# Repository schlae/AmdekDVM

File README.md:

# Amdek DVM Clone

The Amdek DVM allowed RGB digital monitors to be connected to Apple II
computers (which normally output composite video).

This project is a reverse-engineered version of this card.

It uses readily-available TTL logic chips, with no programmable devices at
all.

*Note: The photo shows an original DVM card since I have not fabricated my design*

[Schematic](AmdekDVM.pdf)

[Bill of Materials](AmdekDVM.csv)

[Fab files](fab/AmdekDVM-Rev1.zip)

[Fab files for daughterboard](AmdekDaughterBoard/fab/AmdekDaughterBoard-Rev1.zip)

## Fabrication Notes

The main board is 280mm x 76mm (11" x 3"). It is a simple 2-layer board. It
has an edge connector on the bottom, and you may want to have it gold plated,
but this isn't strictly necessary. No edge bevel is required but it may make
it easier to insert into the connectors on the Apple II (or you could add
one with a file).

The daughterboard is 38mm x 87mm (1.5" x 3.435"). It is a simple 2-layer board
and could even be reduced down to a 1-layer design if you have access to such
a fab process.

## Assembly Notes

RV2 is actually a fixed resistor, 2K. Solder it from pin 1 to pin 3.

C3-C13 are just bypass capacitors and could easily be subbed out with 0.1uF.

C14-C23 are not stuffed on the original board, but it would be harmless
to place 0.1uF capacitors here.

The daughterboard (actually two separate boards, see the photos below) should
have machine-pin sockets installed. To allow them to be plugged into the Apple
II motherboard, solder additional socket pins (harvested from spare sockets)
to the ends of the pins protruding from the other side of the board. Alignment
is critical so that the pins will plug into the sockets on the Apple II.

The daughterboard can be assembled with regular 0.1" headers and 8-pin IDC
plugs, or you can use a combined part like the CA2308PA10Z. The cable is
split exactly in half, with the first 8 pins going to the 4-chip daughterboard
and the second 8 pins going to the 2-chip daughterboard (with wire 9 tied
to pin 1 of this daughterboard).

## Cables

To build this card, you will need a video output cable wired as follows. Plug
it into J2 (nearest the edge connector).

| Pin | Description |
|-----|-------------|
| 1   | Red output |
| 2   | Green output |
| 3   | Blue output |
| 4   | Horizontal sync (positive) |
| 5   | Horizontal sync (negative) |
| 6   | Vertical sync (positive) |
| 7   | Vertical sync (negative) |
| 8   | No connect |
| 9   | Ground |
| 10  | No connect |
| 11  | Apple II text - connect to Apple II header K14 pin 2 |
| 12  | Horizontal sync from 80-column card |
| 13  | Video signal from 80-column card |
| 14  | Vertical sync from 80-column card |

Pin 11 of this cable should be wired to the Apple II video header. On my
Apple II+, it looks like this.

If you want to connect the DVM to a CGA-compatible monitor, wire it up as
follows:

| Amdek Pin | CGA Pin | Description |
|-----------|---------|-------------|
| 1         |  3      | Red output  |
| 2         |  4      | Green output |
| 3         |  5      | Blue output |
| 4         |  8      | Horizontal sync (positive) |
| 6         |  9      | Vertical sync (positive) |
| 9         |  1      | Ground |

If you have an 80-column card, you can wire pins 12-14 to that card as
appropriate.

You will also need a cable connected to J1 (furthest from the edge connector)
wired to two daughterboards. The daughterboards act as interposers, tapping
various signals on the Apple II motherboard.

* One daughterboard sits on motherboard positions D11, D12, D13, and D14,
hosting the four 74LS161 chips that the Apple II uses to generate the video
timing signals. It intercepts three horizontal counter bits and five vertical
counter bits.

* The other daughterboard sits on motherboard positions B6 and B7, hosting
two 74LS257 chips. This intercepts the eight digital video bits before
they go through encoding to composite video.

## Adjustments

When you install the card, ensure you get video out of your Apple II, then
adjust RV1 until you get stable pixels.

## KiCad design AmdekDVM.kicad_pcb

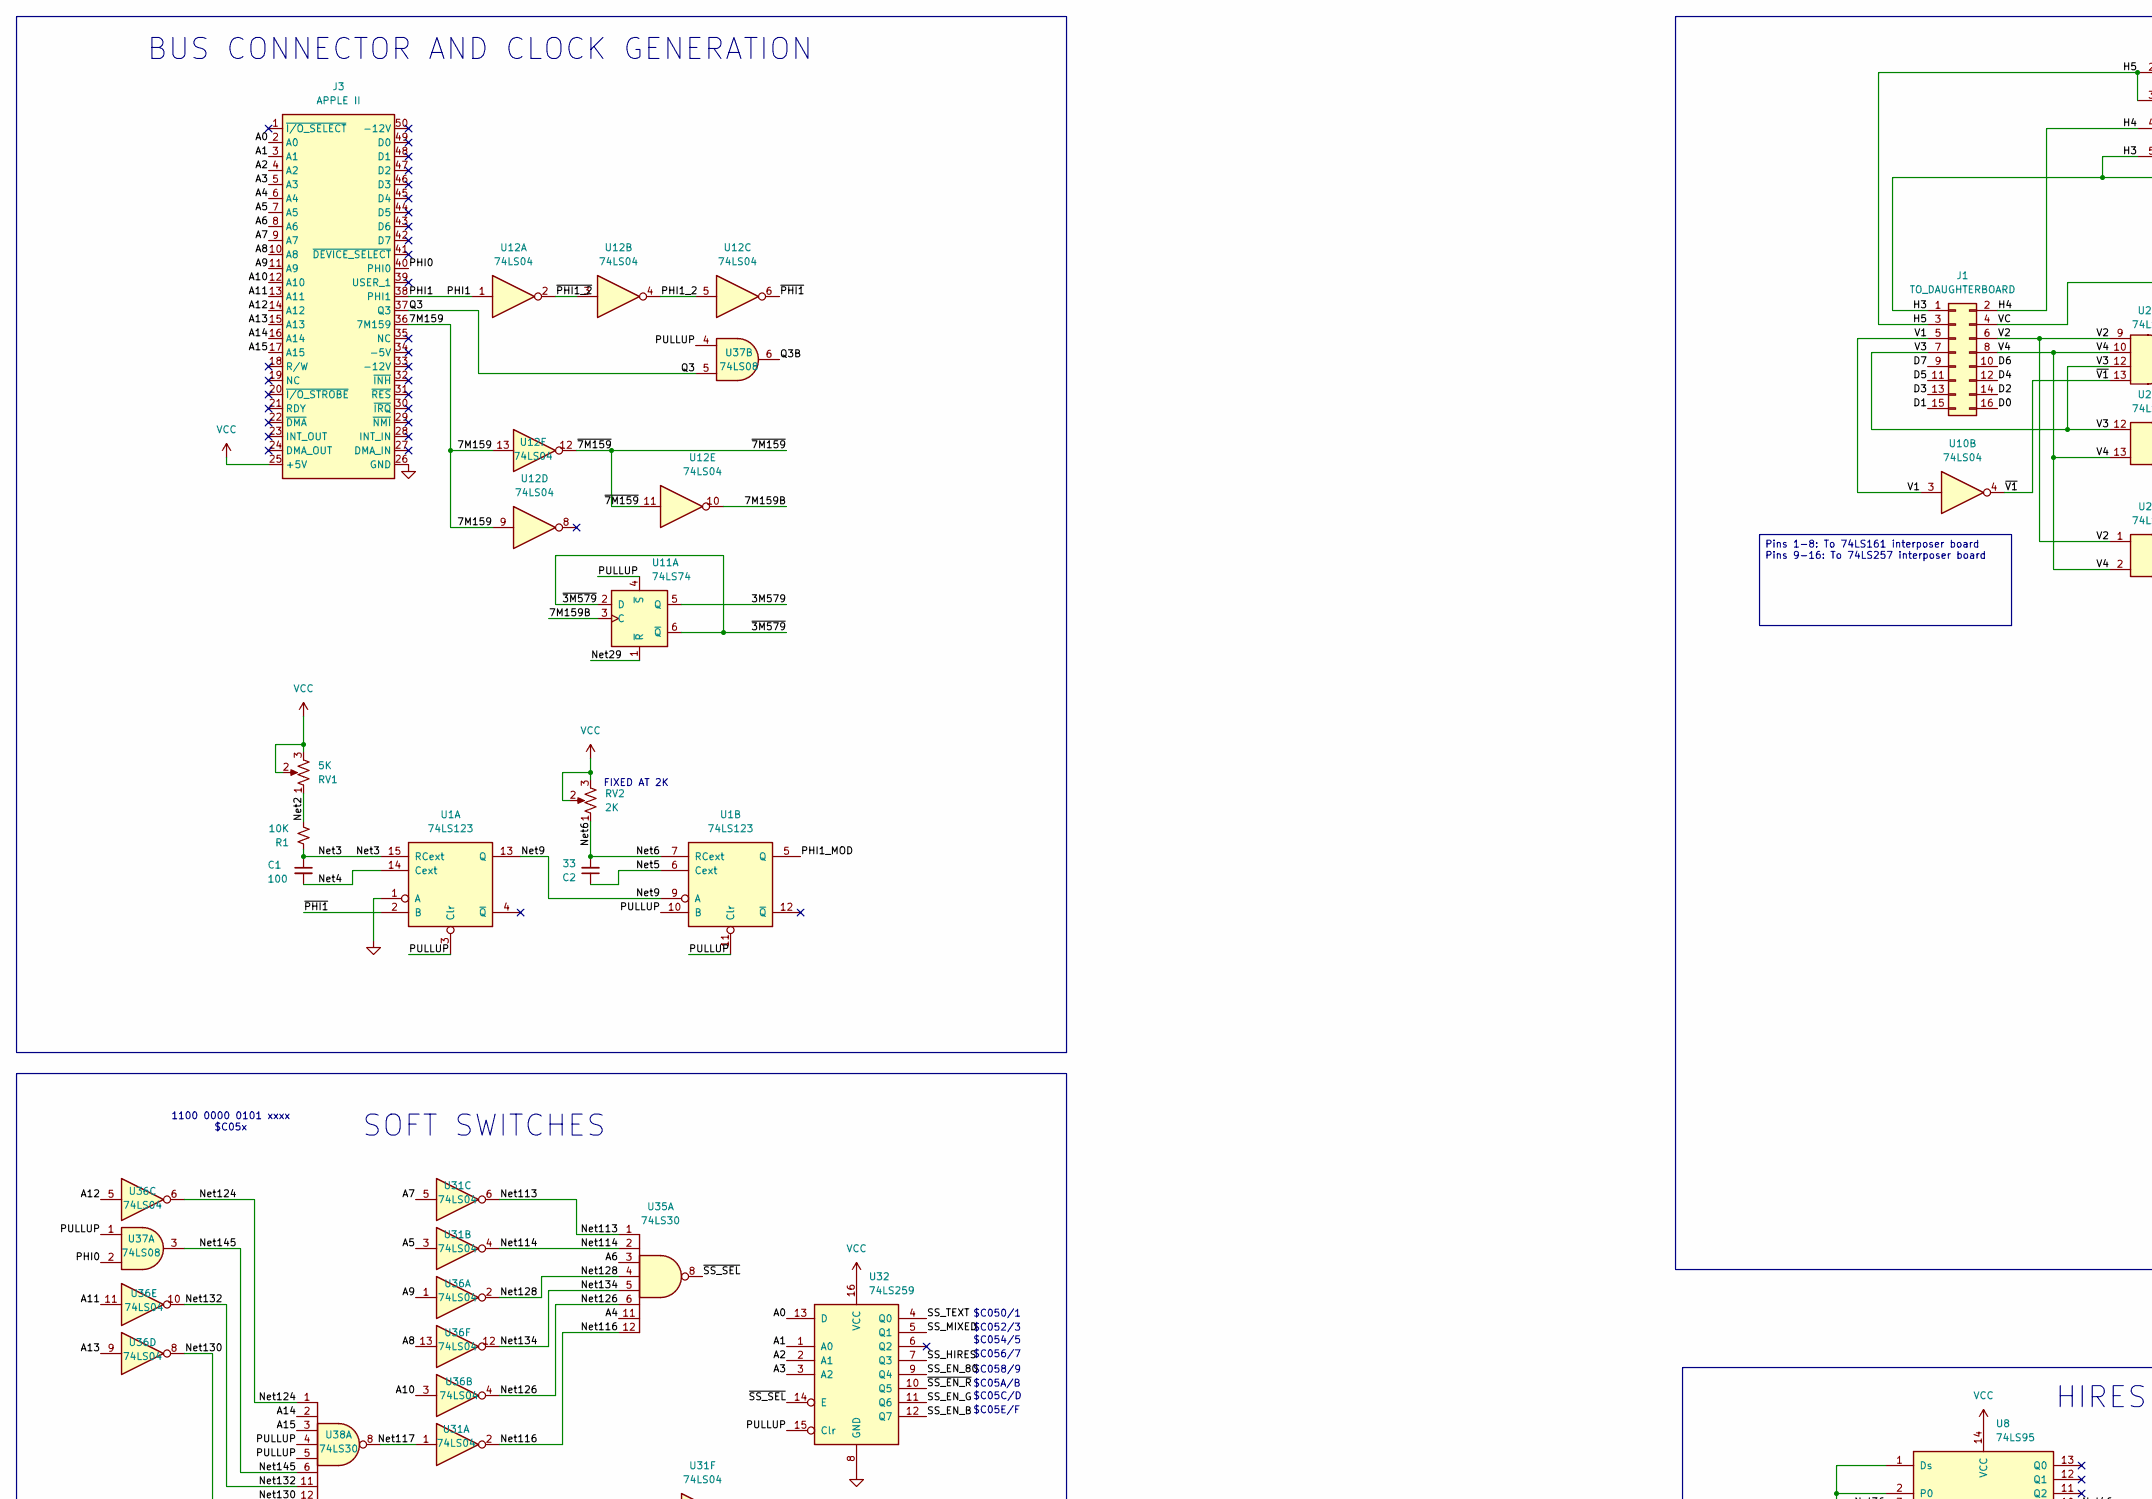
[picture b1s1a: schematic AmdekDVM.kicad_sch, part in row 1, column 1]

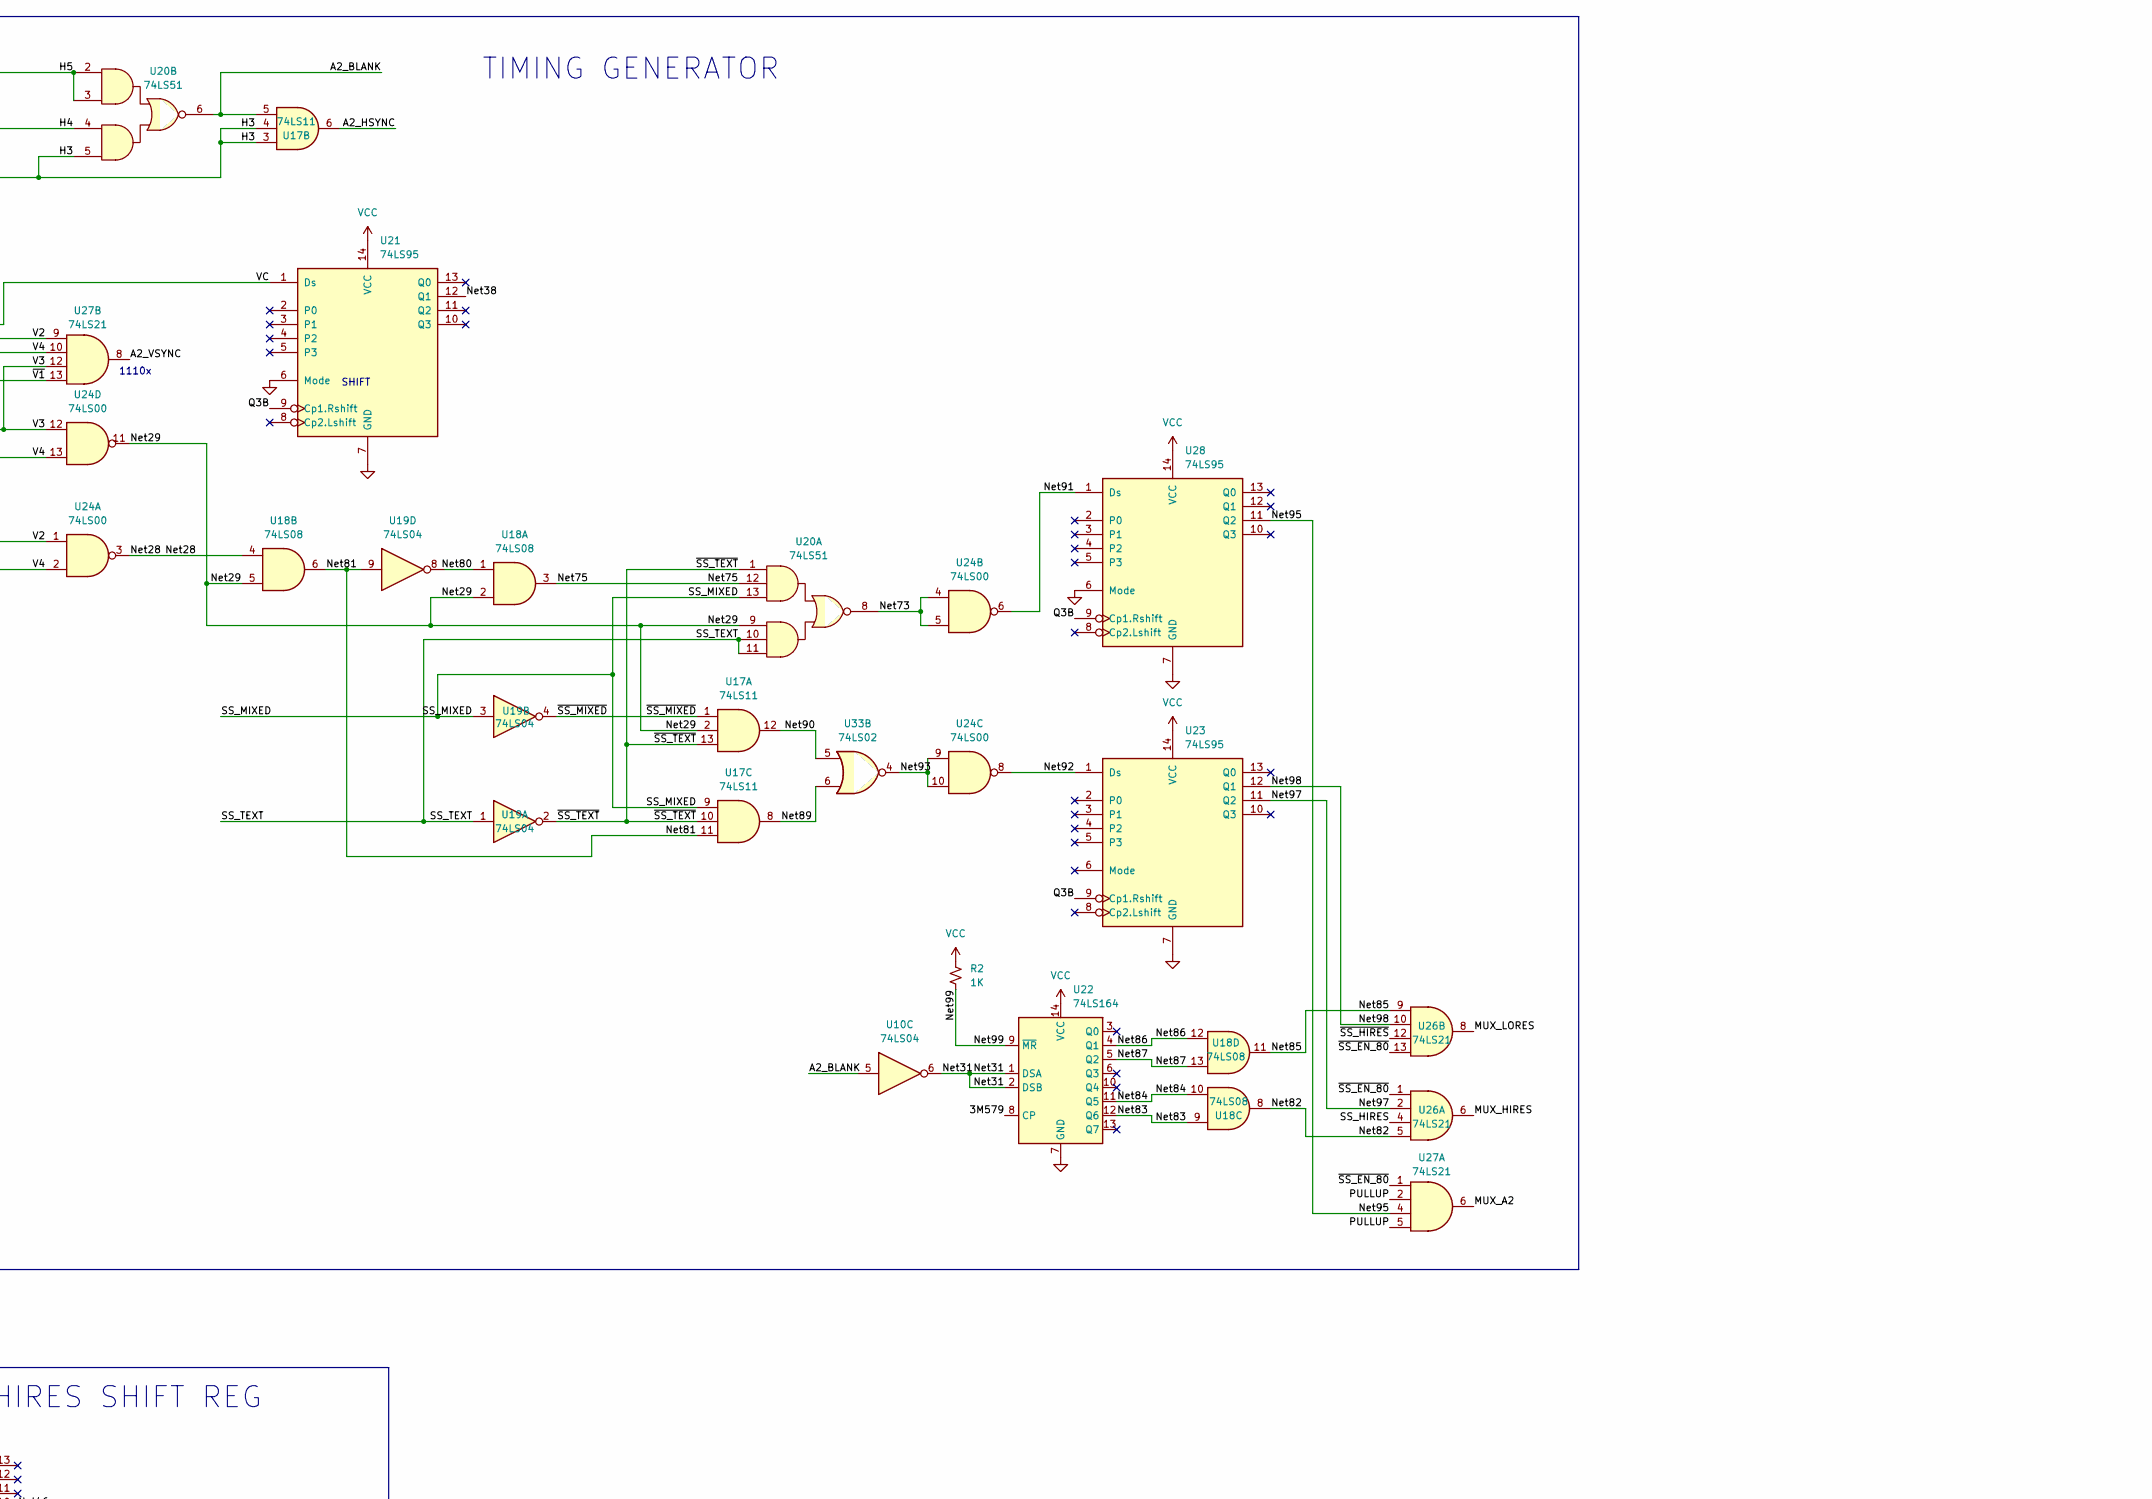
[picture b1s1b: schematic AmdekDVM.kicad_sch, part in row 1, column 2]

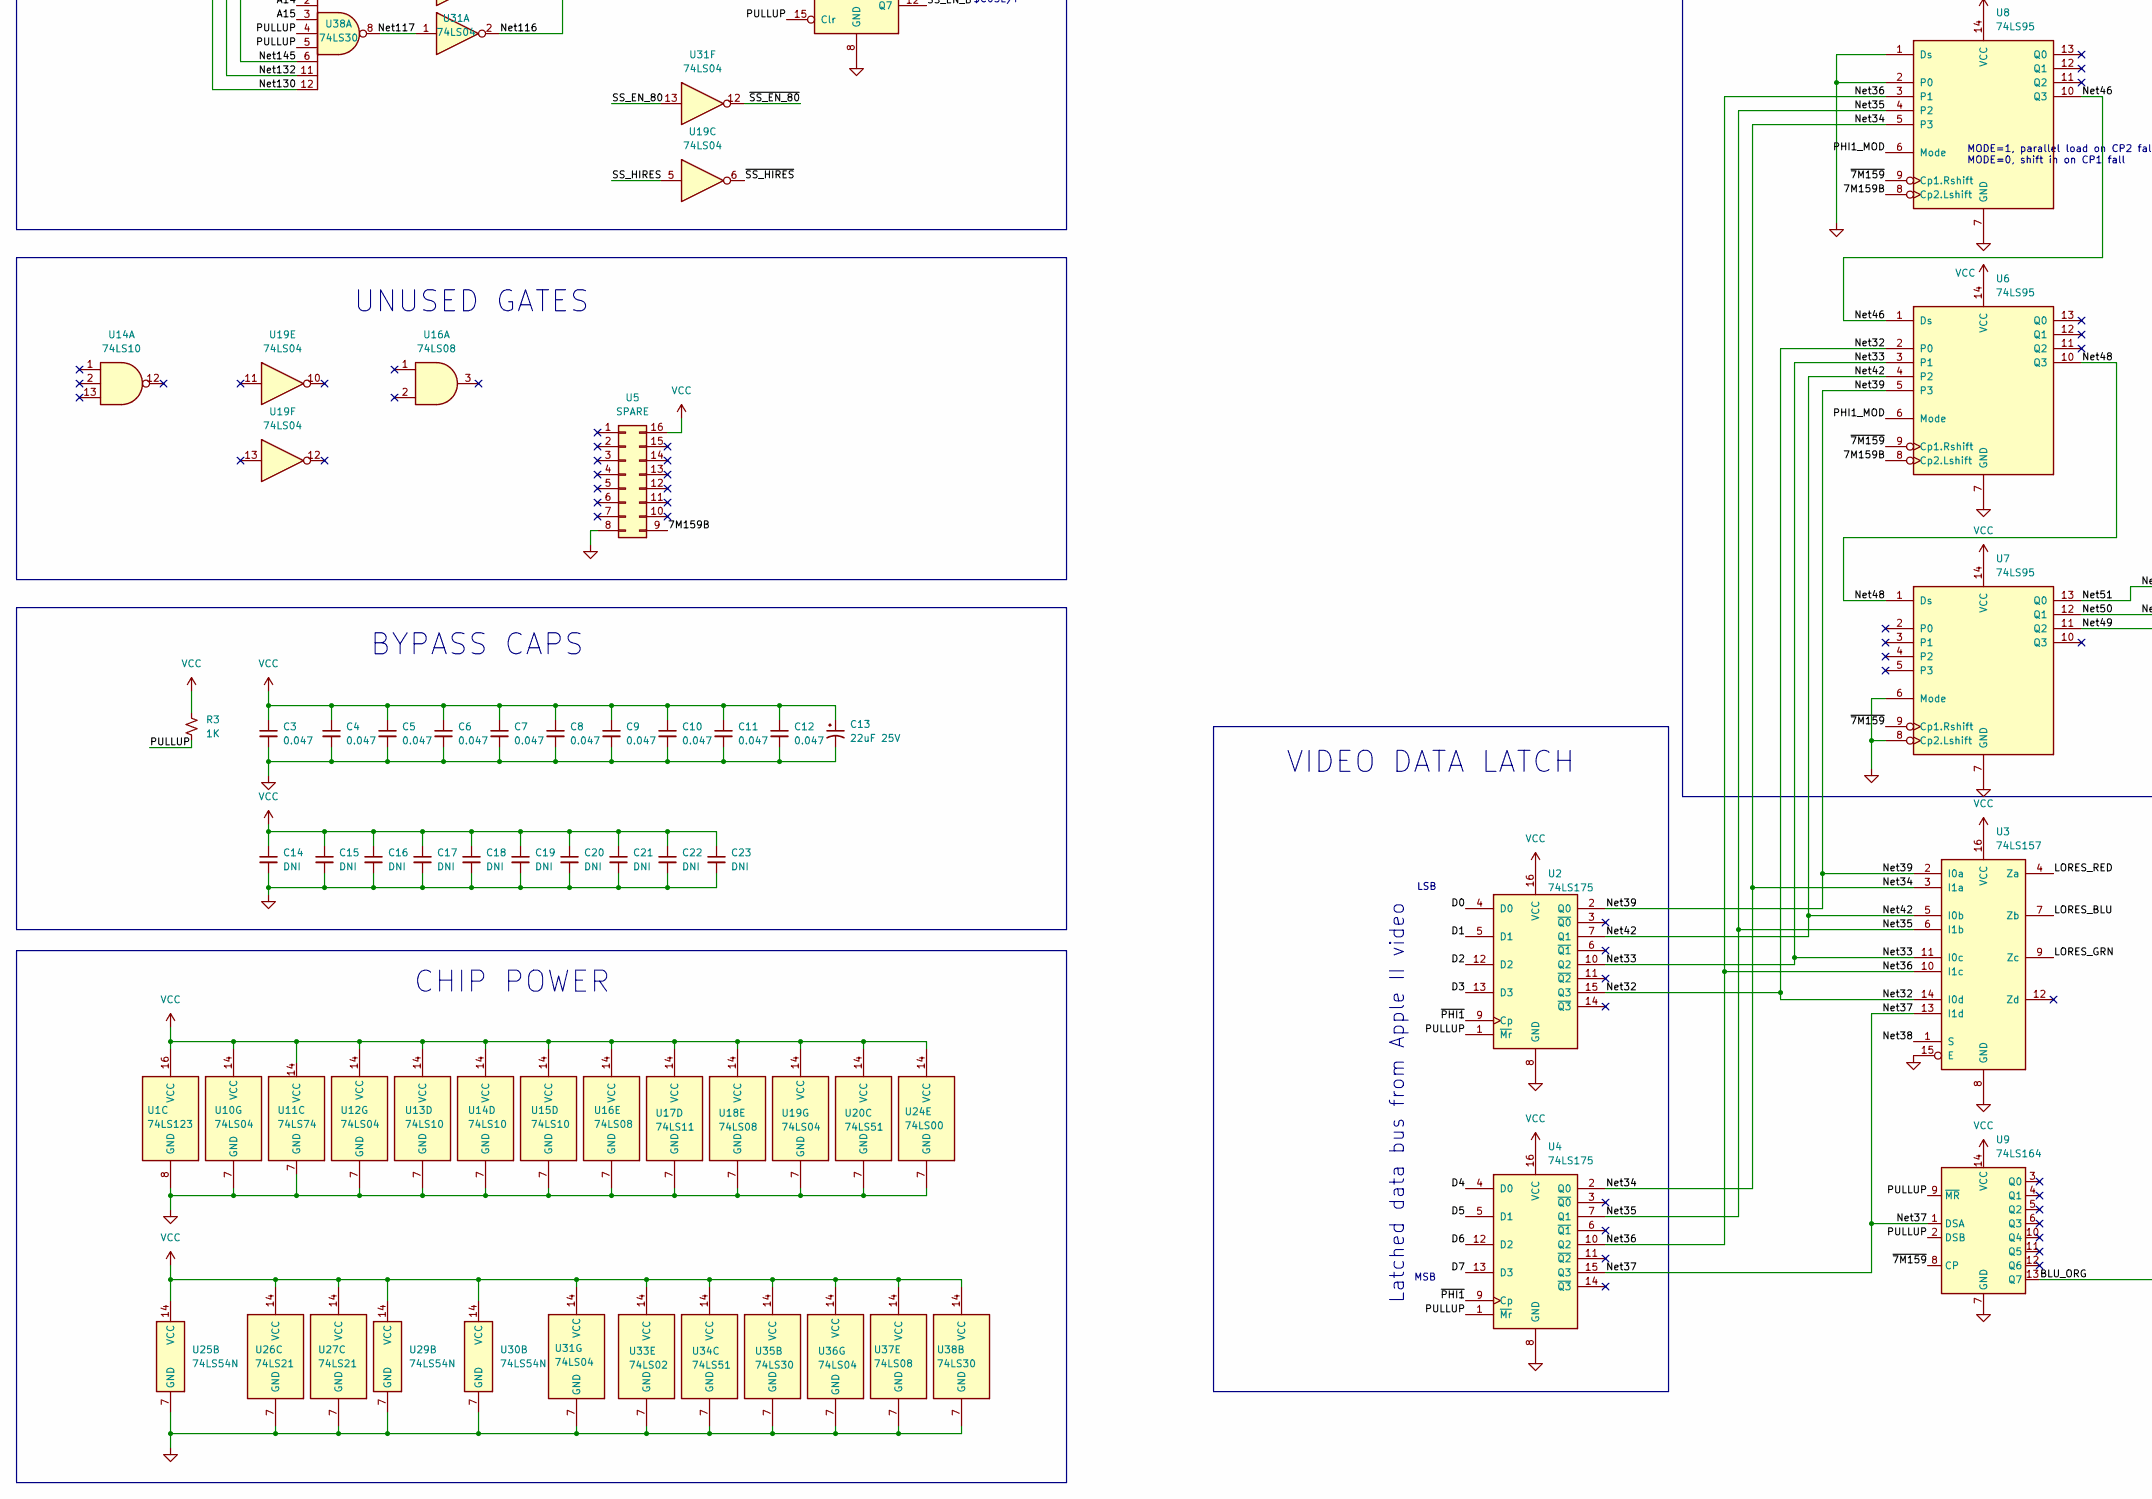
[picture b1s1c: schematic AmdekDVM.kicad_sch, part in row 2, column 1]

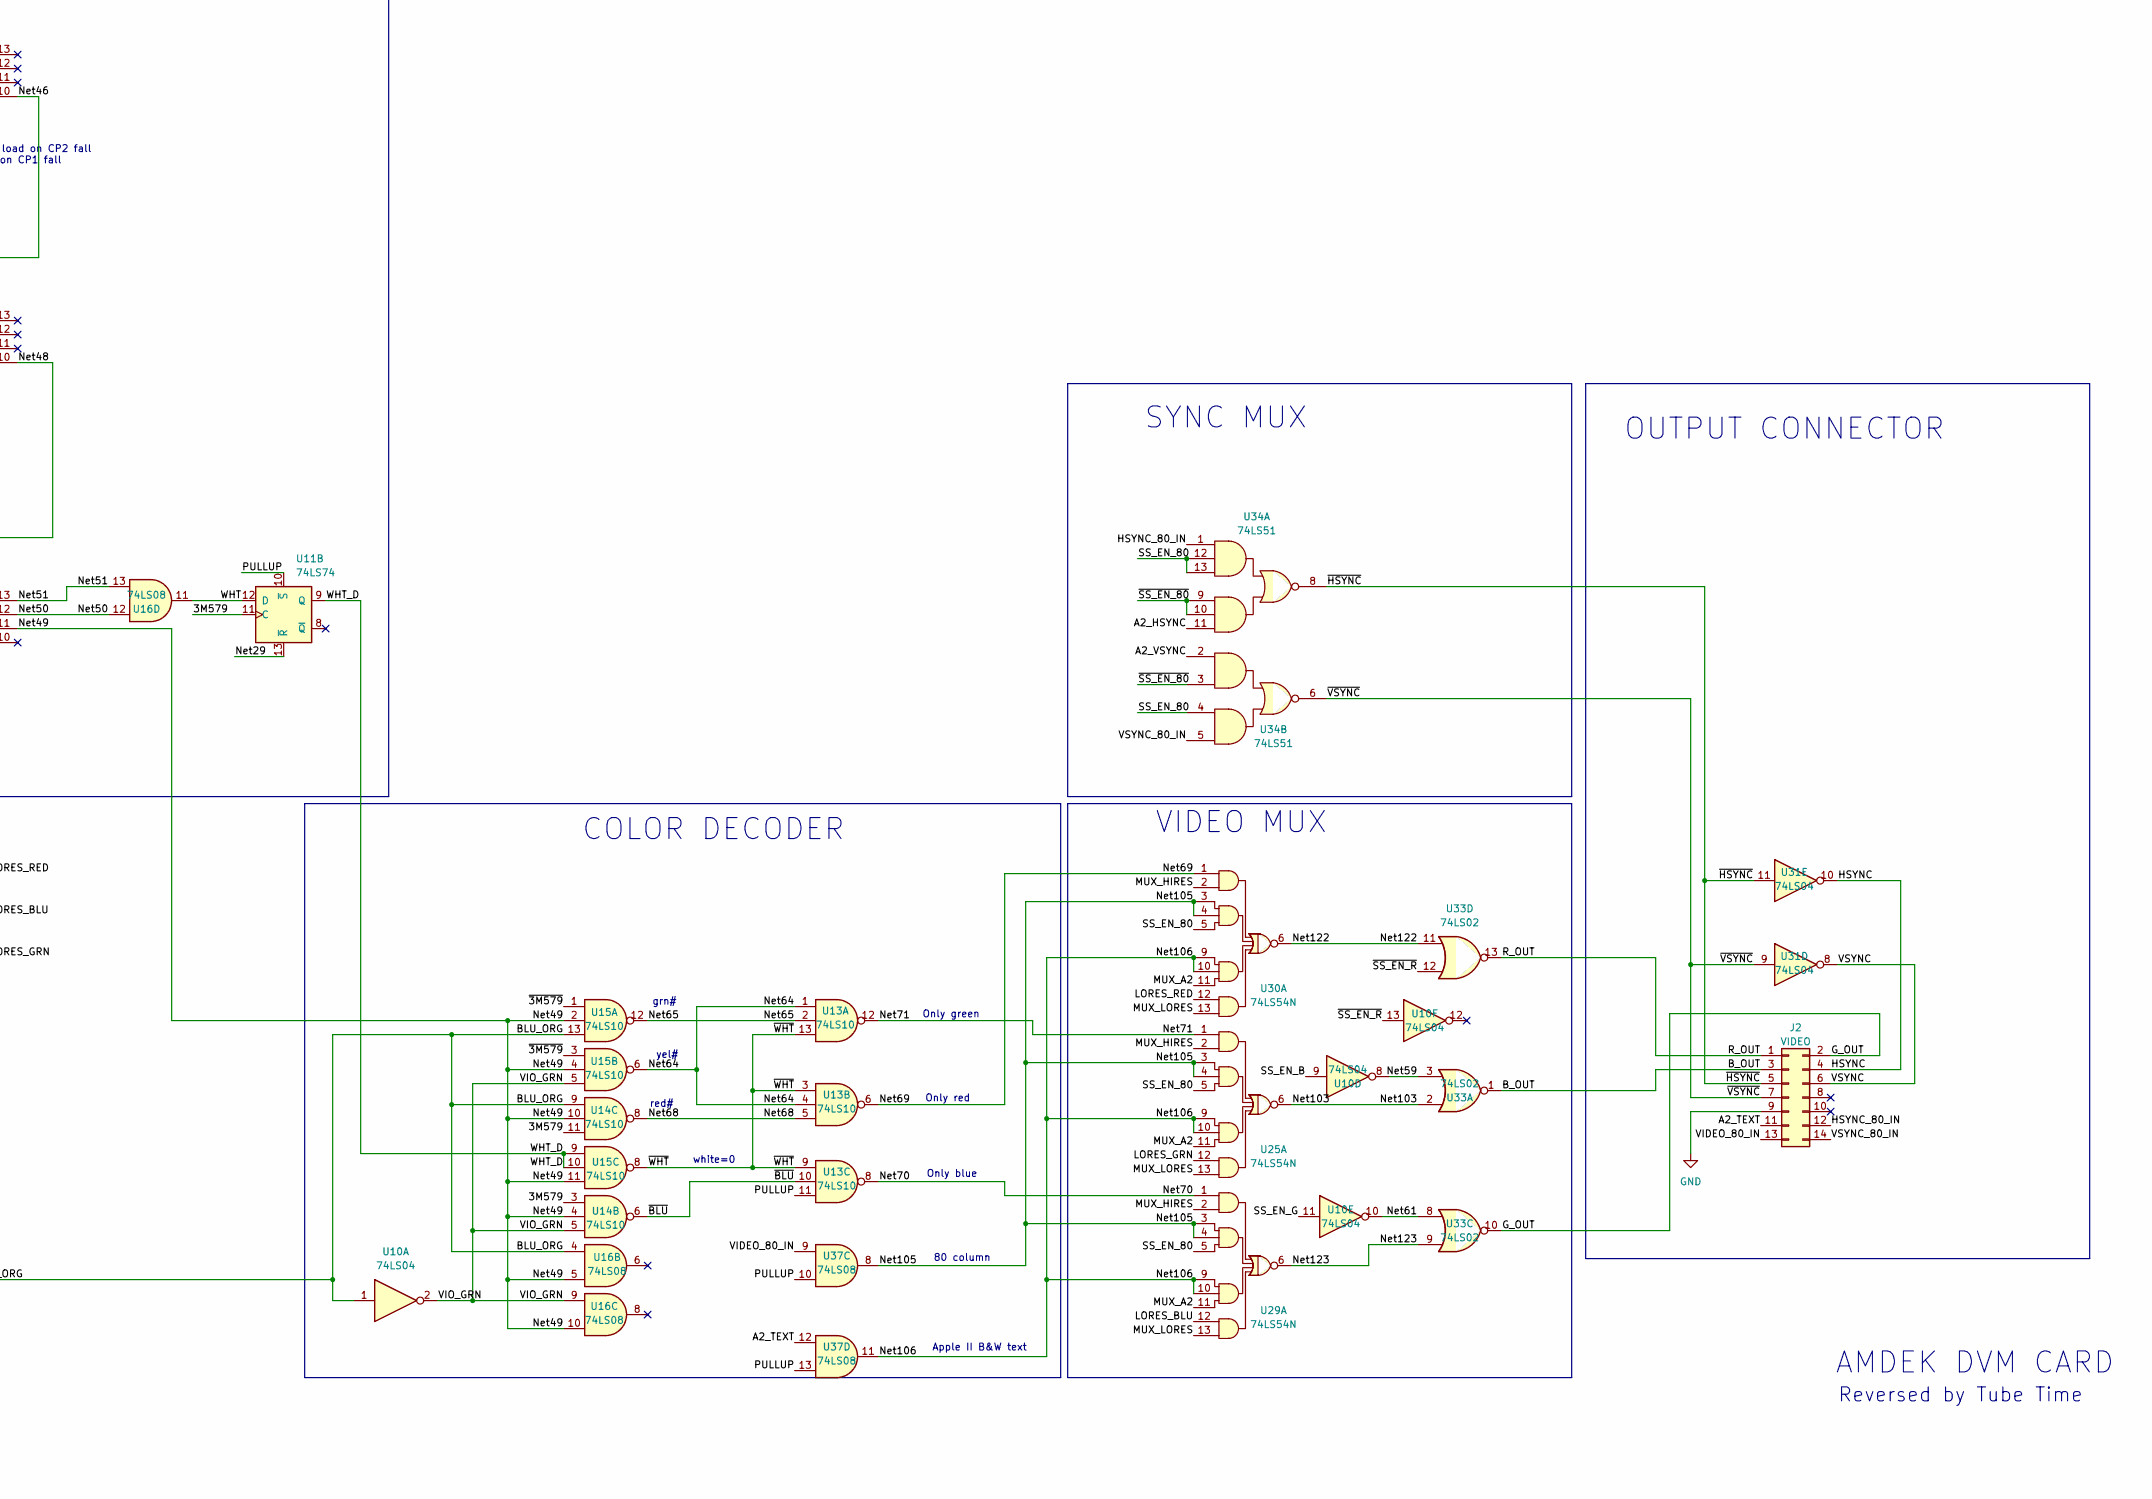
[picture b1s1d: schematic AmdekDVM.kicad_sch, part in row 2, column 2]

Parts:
C1: 100; C_Disc_D4.3mm_W1.9mm_P5.00mm
C2: 33; C_Disc_D4.3mm_W1.9mm_P5.00mm
C3, C4, C5, C6, C7, C8, C9, C10, C11, C12: 0.047; C_Disc_D4.3mm_W1.9mm_P5.00mm
C13: 22uF 25V; CP_Axial_L10.0mm_D4.5mm_P15.00mm_Horizontal
C14, C15, C16, C17, C18, C19, C20, C21, C22, C23: DNI; C_Disc_D4.3mm_W1.9mm_P5.00mm
J1: TO_DAUGHTERBOARD; PinHeader_2x08_P2.54mm_Horizontal
J2: VIDEO; PinHeader_2x07_P2.54mm_Horizontal
J3: APPLE II; APPLE_II
R1: 10K; R_Axial_DIN0309_L9.0mm_D3.2mm_P12.70mm_Horizontal
R2, R3: 1K; R_Axial_DIN0309_L9.0mm_D3.2mm_P12.70mm_Horizontal
RV1: 5K; Potentiometer_Bourns_3006P_Horizontal
RV2: 2K; Potentiometer_Bourns_3006P_Horizontal
U1: 74LS123; DIP-16_W7.62mm
U2, U4: 74LS175; DIP-16_W7.62mm
U3: 74LS157; DIP-16_W7.62mm
U5: SPARE; DIP-16_W7.62mm
U6, U7, U8, U21, U23, U28: 74LS95; DIP-14_W7.62mm
U9, U22: 74LS164; DIP-14_W7.62mm
U10, U12, U19, U31, U36: 74LS04; DIP-14_W7.62mm
U11: 74LS74; DIP-14_W7.62mm
U13, U14, U15: 74LS10; DIP-14_W7.62mm
U16, U18, U37: 74LS08; DIP-14_W7.62mm
U17: 74LS11; DIP-14_W7.62mm
U20, U34: 74LS51; DIP-14_W7.62mm
U24: 74LS00; DIP-14_W7.62mm
U25, U29, U30: 74LS54N; DIP-14_W7.62mm
U26, U27: 74LS21; DIP-14_W7.62mm
U32: 74LS259; DIP-16_W7.62mm
U33: 74LS02; DIP-14_W7.62mm
U35, U38: 74LS30; DIP-14_W7.62mm

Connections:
/3M579: U11.5 (Q), U11.11 (C), U14.3, U14.11, U22.8 (CP)
/7M159: J3.36 (7M159), U12.9, U12.13
/7M159B: U5.9, U6.8 (Cp2.Lshift), U8.8 (Cp2.Lshift), U11.3 (C), U12.10
/A0: J3.2 (A0), U32.13 (D)
/A1: J3.3 (A1), U32.1 (A0)
/A2: J3.4 (A2), U32.2 (A1)
/A2_BLANK: U10.5, U17.5, U20.6
/A2_HSYNC: U17.6, U34.11
/A2_TEXT: J2.11, U37.12
/A2_VSYNC: U27.8, U34.2
/A3: J3.5 (A3), U32.3 (A2)
/A4: J3.6 (A4), U35.11
/A5: J3.7 (A5), U31.3
/A6: J3.8 (A6), U35.3
/A7: J3.9 (A7), U31.5
/A8: J3.10 (A8), U36.13
/A9: J3.11 (A9), U36.1
/A10: J3.12 (A10), U36.3
/A11: J3.13 (A11), U36.11
/A12: J3.14 (A12), U36.5
/A13: J3.15 (A13), U36.9
/A14: J3.16 (A14), U38.2
/A15: J3.17 (A15), U38.3
/BLU_ORG: U9.13 (Q7), U10.1, U14.9, U15.13, U16.4
/B_OUT: J2.3, U33.1
/D0: J1.16, U2.4 (D0)
/D1: J1.15, U2.5 (D1)
/D2: J1.14, U2.12 (D2)
/D3: J1.13, U2.13 (D3)
/D4: J1.12, U4.4 (D0)
/D5: J1.11, U4.5 (D1)
/D6: J1.10, U4.12 (D2)
/D7: J1.9, U4.13 (D3)
/G_OUT: J2.2, U33.10
/H3: J1.1, U17.3, U17.4, U20.5
/H4: J1.2, U20.4
/H5: J1.3, U20.2, U20.3
/HSYNC: J2.4, U31.10
/HSYNC_80_IN: J2.12, U34.1
/LORES_BLU: U3.7 (Zb), U29.12
/LORES_GRN: U3.9 (Zc), U25.12
/LORES_RED: U3.4 (Za), U30.12
/MUX_A2: U25.11, U27.6, U29.11, U30.11
/MUX_HIRES: U25.2, U26.6, U29.2, U30.2
/MUX_LORES: U25.13, U26.8, U29.13, U30.13
/Net2: R1.2, RV1.1
/Net3: C1.1, R1.1, U1.15 (RCext)
/Net4: C1.2, U1.14 (Cext)
/Net5: C2.1, U1.6 (Cext)
/Net6: C2.2, RV2.1, U1.7 (RCext)
/Net9: U1.9 (A), U1.13 (Q)
/Net28: U18.4, U24.3
/Net29: U11.1 (~R), U11.13 (~R), U17.2, U18.2, U18.5, U20.9, U24.11
/Net31: U10.6, U22.1 (DSA), U22.2 (DSB)
/Net32: U2.15 (Q3), U3.14 (I0d), U6.2 (P0)
/Net33: U2.10 (Q2), U3.11 (I0c), U6.3 (P1)
/Net34: U3.3 (I1a), U4.2 (Q0), U8.5 (P3)
/Net35: U3.6 (I1b), U4.7 (Q1), U8.4 (P2)
/Net36: U3.10 (I1c), U4.10 (Q2), U8.3 (P1)
/Net37: U3.13 (I1d), U4.15 (Q3), U9.1 (DSA)
/Net38: U3.1 (S), U21.12 (Q1)
/Net39: U2.2 (Q0), U3.2 (I0a), U6.5 (P3)
/Net42: U2.7 (Q1), U3.5 (I0b), U6.4 (P2)
/Net46: U6.1 (Ds), U8.10 (Q3)
/Net48: U6.10 (Q3), U7.1 (Ds)
/Net49: U7.11 (Q2), U14.4, U14.10, U15.2, U15.4, U15.11, U16.5, U16.10
/Net50: U7.12 (Q1), U16.12
/Net51: U7.13 (Q0), U16.13
/Net59: U10.8, U33.3
/Net61: U10.10, U33.8
/Net64: U13.1, U13.4, U15.6
/Net65: U13.2, U15.12
/Net68: U13.5, U14.8
/Net69: U13.6, U30.1
/Net70: U13.8, U29.1
/Net71: U13.12, U25.1
/Net73: U20.8, U24.4, U24.5
/Net75: U18.3, U20.12
/Net80: U18.1, U19.8
/Net81: U17.11, U18.6, U19.9
/Net82: U18.8, U26.5
/Net83: U18.9, U22.12 (Q6)
/Net84: U18.10, U22.11 (Q5)
/Net85: U18.11, U26.9
/Net86: U18.12, U22.4 (Q1)
/Net87: U18.13, U22.5 (Q2)
/Net89: U17.8, U33.6
/Net90: U17.12, U33.5
/Net91: U24.6, U28.1 (Ds)
/Net92: U23.1 (Ds), U24.8
/Net93: U24.9, U24.10, U33.4
/Net95: U27.4, U28.11 (Q2)
/Net97: U23.11 (Q2), U26.2
/Net98: U23.12 (Q1), U26.10
/Net99: R2.2, U22.9 (~MR)
/Net103: U25.6, U33.2
/Net105: U25.3, U25.4, U29.3, U29.4, U30.3, U30.4, U37.8
/Net106: U25.9, U25.10, U29.9, U29.10, U30.9, U30.10, U37.11
/Net113: U31.6, U35.1
/Net114: U31.4, U35.2
/Net116: U31.2, U35.12
/Net117: U31.1, U38.8
/Net122: U30.6, U33.11
/Net123: U29.6, U33.9
/Net124: U36.6, U38.1
/Net126: U35.6, U36.4
/Net128: U35.4, U36.2
/Net130: U36.8, U38.12
/Net132: U36.10, U38.11
/Net134: U35.5, U36.12
/Net145: U37.3, U38.6
/PHI0: J3.40 (PHI0), U37.2
/PHI1: J3.38 (PHI1), U12.1
/PHI1_2: U12.4, U12.5
/PHI1_MOD: U1.5 (Q), U6.6 (Mode), U8.6 (Mode)
/PULLUP: R3.2, U1.3 (Clr), U1.10 (B), U1.11 (Clr), U2.1 (~Mr), U4.1 (~Mr), U9.2 (DSB), U9.9 (~MR), U11.4 (~S), U11.10 (~S), U13.11, U27.2, U27.5, U32.15 (Clr), U37.1, U37.4, U37.10, U37.13, U38.4, U38.5
/Q3: J3.37 (Q3), U37.5
/Q3B: U21.9 (Cp1.Rshift), U23.9 (Cp1.Rshift), U28.9 (Cp1.Rshift), U37.6
/R_OUT: J2.1, U33.13
/SS_EN_80: U25.5, U29.5, U30.5, U31.13, U32.9 (Q4), U34.4, U34.12, U34.13
/SS_EN_B: U10.9, U32.12 (Q7)
/SS_EN_G: U10.11, U32.11 (Q6)
/SS_HIRES: U19.5, U26.4, U32.7 (Q3)
/SS_MIXED: U17.9, U19.3, U20.13, U32.5 (Q1)
/SS_TEXT: U19.1, U20.10, U20.11, U32.4 (Q0)
/V1: J1.5, U10.3
/V2: J1.6, U24.1, U27.9
/V3: J1.7, U24.12, U27.12
/V4: J1.8, U24.2, U24.13, U27.10
/VC: J1.4, U21.1 (Ds)
/VIDEO_80_IN: J2.13, U37.9
/VIO_GRN: U10.2, U14.5, U15.5, U16.9
/VSYNC: J2.6, U31.8
/VSYNC_80_IN: J2.14, U34.5
/WHT: U11.12 (D), U16.11
/WHT_D: U11.9 (Q), U15.9, U15.10
/~3M579: U11.2 (D), U11.6 (~Q), U15.1, U15.3
/~7M159: U6.9 (Cp1.Rshift), U7.9 (Cp1.Rshift), U8.9 (Cp1.Rshift), U9.8 (CP), U12.11, U12.12
/~BLU: U13.10, U14.6
/~HSYNC: J2.5, U31.11, U34.8
/~PHI1_2: U12.2, U12.3
/~PHI1: U1.2 (B), U2.9 (Cp), U4.9 (Cp), U12.6
/~SS_EN_80: U26.1, U26.13, U27.1, U31.12, U34.3, U34.9, U34.10
/~SS_EN_R: U10.13, U32.10 (Q5), U33.12
/~SS_HIRES: U19.6, U26.12
/~SS_MIXED: U17.1, U19.4
/~SS_SEL: U32.14 (E), U35.8
/~SS_TEXT: U17.10, U17.13, U19.2, U20.1
/~V1: U10.4, U27.13
/~VSYNC: J2.7, U31.9, U34.6
/~WHT: U13.3, U13.9, U13.13, U15.8
GND: C3.2, C4.2, C5.2, C6.2, C7.2, C8.2, C9.2, C10.2, C11.2, C12.2, C13.2, C14.2, C15.2, C16.2, C17.2, C18.2, C19.2, C20.2, C21.2, C22.2, C23.2, J2.9, J3.26 (GND), U1.1 (A), U1.8 (GND), U2.8 (GND), U3.8 (GND), U3.15 (E), U4.8 (GND), U5.8, U6.7 (GND), U7.6 (Mode), U7.7 (GND), U7.8 (Cp2.Lshift), U8.1 (Ds), U8.2 (P0), U8.7 (GND), U9.7 (GND), U10.7 (GND), U11.7 (GND), U12.7 (GND), U13.7 (GND), U14.7 (GND), U15.7 (GND), U16.7 (GND), U17.7 (GND), U18.7 (GND), U19.7 (GND), U20.7 (GND), U21.6 (Mode), U21.7 (GND), U22.7 (GND), U23.7 (GND), U24.7 (GND), U25.7 (GND), U26.7 (GND), U27.7 (GND), U28.6 (Mode), U28.7 (GND), U29.7 (GND), U30.7 (GND), U31.7 (GND), U32.8 (GND), U33.7 (GND), U34.7 (GND), U35.7 (GND), U36.7 (GND), U37.7 (GND), U38.7 (GND)
VCC: C3.1, C4.1, C5.1, C6.1, C7.1, C8.1, C9.1, C10.1, C11.1, C12.1, C13.1, C14.1, C15.1, C16.1, C17.1, C18.1, C19.1, C20.1, C21.1, C22.1, C23.1, J3.25 (+5V), R2.1, R3.1, RV1.2, RV1.3, RV2.2, RV2.3, U1.16 (VCC), U2.16 (VCC), U3.16 (VCC), U4.16 (VCC), U5.16, U6.14 (VCC), U7.14 (VCC), U8.14 (VCC), U9.14 (VCC), U10.14 (VCC), U11.14 (VCC), U12.14 (VCC), U13.14 (VCC), U14.14 (VCC), U15.14 (VCC), U16.14 (VCC), U17.14 (VCC), U18.14 (VCC), U19.14 (VCC), U20.14 (VCC), U21.14 (VCC), U22.14 (VCC), U23.14 (VCC), U24.14 (VCC), U25.14 (VCC), U26.14 (VCC), U27.14 (VCC), U28.14 (VCC), U29.14 (VCC), U30.14 (VCC), U31.14 (VCC), U32.16 (VCC), U33.14 (VCC), U34.14 (VCC), U35.14 (VCC), U36.14 (VCC), U37.14 (VCC), U38.14 (VCC)

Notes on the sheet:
CHIP POWER
UNUSED GATES
$C050/1
TIMING GENERATOR
FIXED AT 2K
SOFT SWITCHES
Latched data bus from Apple II video
OUTPUT CONNECTOR
BUS CONNECTOR AND CLOCK GENERATION
white=0
AMDEK DVM CARD
$C056/7
$C058/9
red#
$C05C/D
VIDEO MUX
1100 0000 0101 xxxx $C05x
HIRES SHIFT REG
80 column
COLOR DECODER
SYNC MUX
grn#
Only blue
1110x
VIDEO DATA LATCH
LSB
Reversed by Tube Time
MSB
SHIFT
$C052/3
Apple II B&W text
BYPASS CAPS
yel#
$C05E/F
$C054/5
MODE=1, parallel load on CP2 fall MODE=0, shift in on CP1 fall
Only green
$C05A/B
Only red
Pins 1-8: To 74LS161 interposer board Pins 9-16: To 74LS257 interposer board

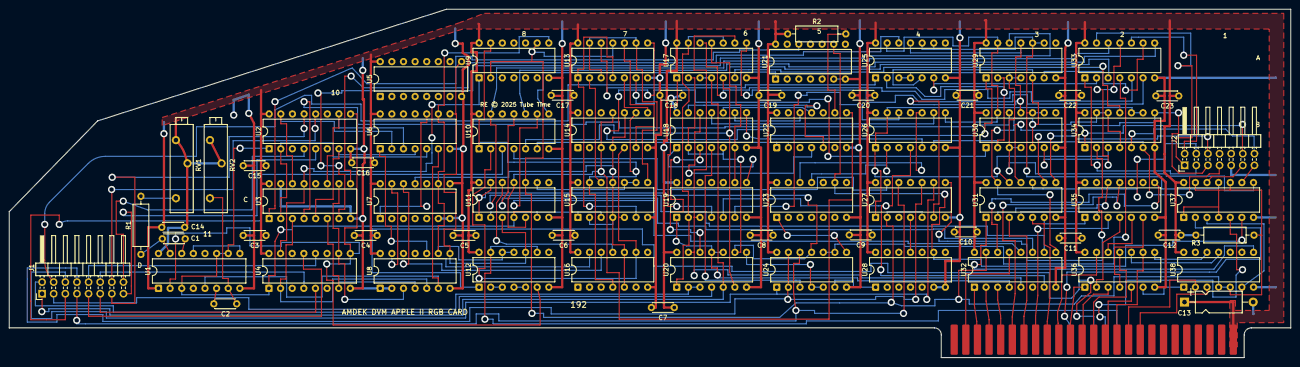
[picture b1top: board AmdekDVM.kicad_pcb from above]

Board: 2 copper layers, 279.9 x 76.1 mm, 69 parts (0 on the bottom side), 153 nets.

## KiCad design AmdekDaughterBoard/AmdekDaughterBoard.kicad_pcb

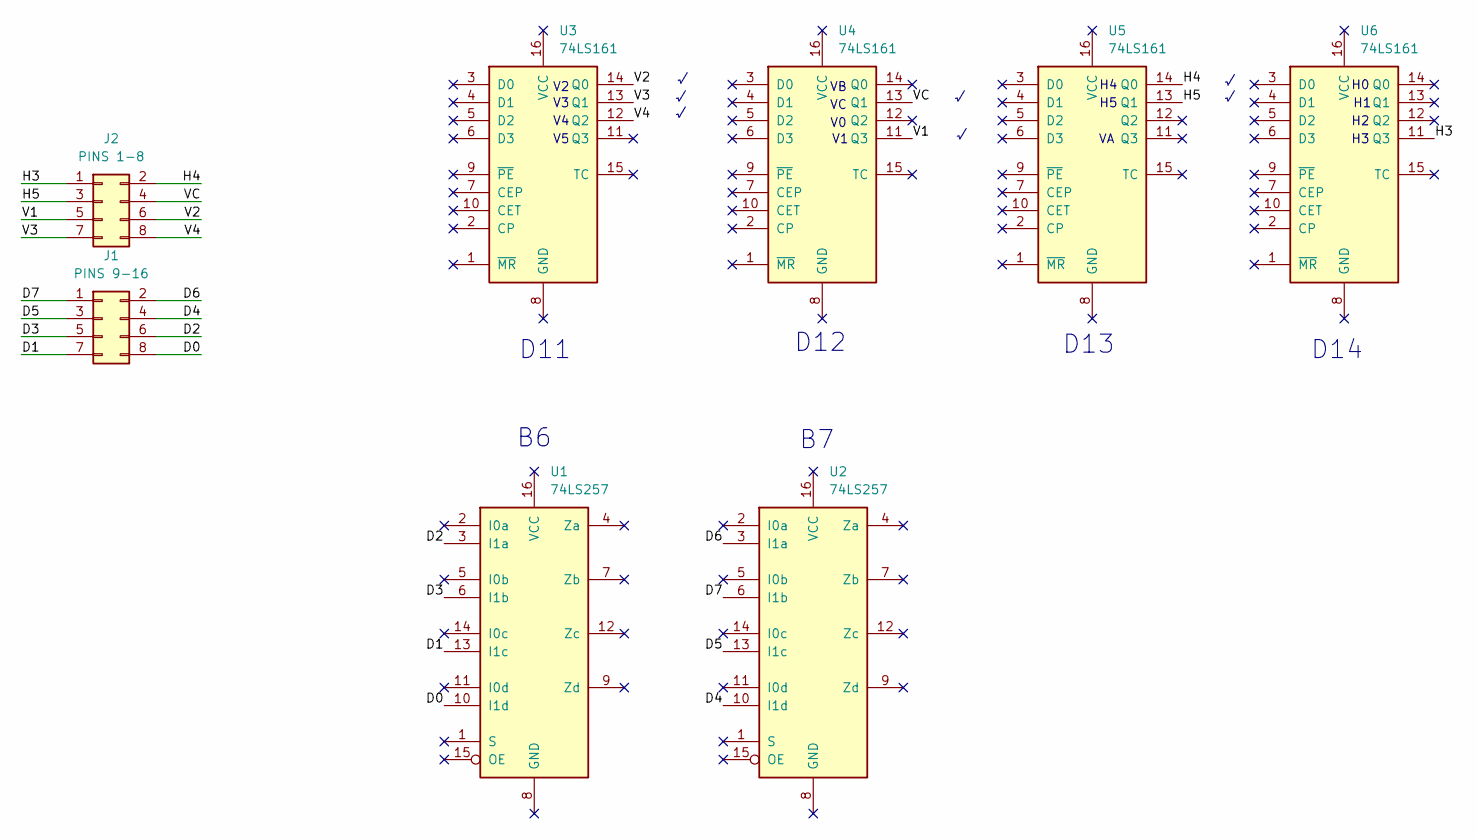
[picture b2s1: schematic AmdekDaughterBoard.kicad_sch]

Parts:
J1: PINS 9-16; PinHeader_2x04_P2.54mm_Vertical
J2: PINS 1-8; PinHeader_2x04_P2.54mm_Vertical
U1, U2: 74LS257; DIP-16_W7.62mm_Socket
U3, U4, U5, U6: 74LS161; DIP-16_W7.62mm_Socket

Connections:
/D0: J1.8, U1.10 (I1d)
/D1: J1.7, U1.13 (I1c)
/D2: J1.6, U1.3 (I1a)
/D3: J1.5, U1.6 (I1b)
/D4: J1.4, U2.10 (I1d)
/D5: J1.3, U2.13 (I1c)
/D6: J1.2, U2.3 (I1a)
/D7: J1.1, U2.6 (I1b)
/H3: J2.1, U6.11 (Q3)
/H4: J2.2, U5.14 (Q0)
/H5: J2.3, U5.13 (Q1)
/V1: J2.5, U4.11 (Q3)
/V2: J2.6, U3.14 (Q0)
/V3: J2.7, U3.13 (Q1)
/V4: J2.8, U3.12 (Q2)
/VC: J2.4, U4.13 (Q1)

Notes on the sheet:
D13
D14
D11
D12

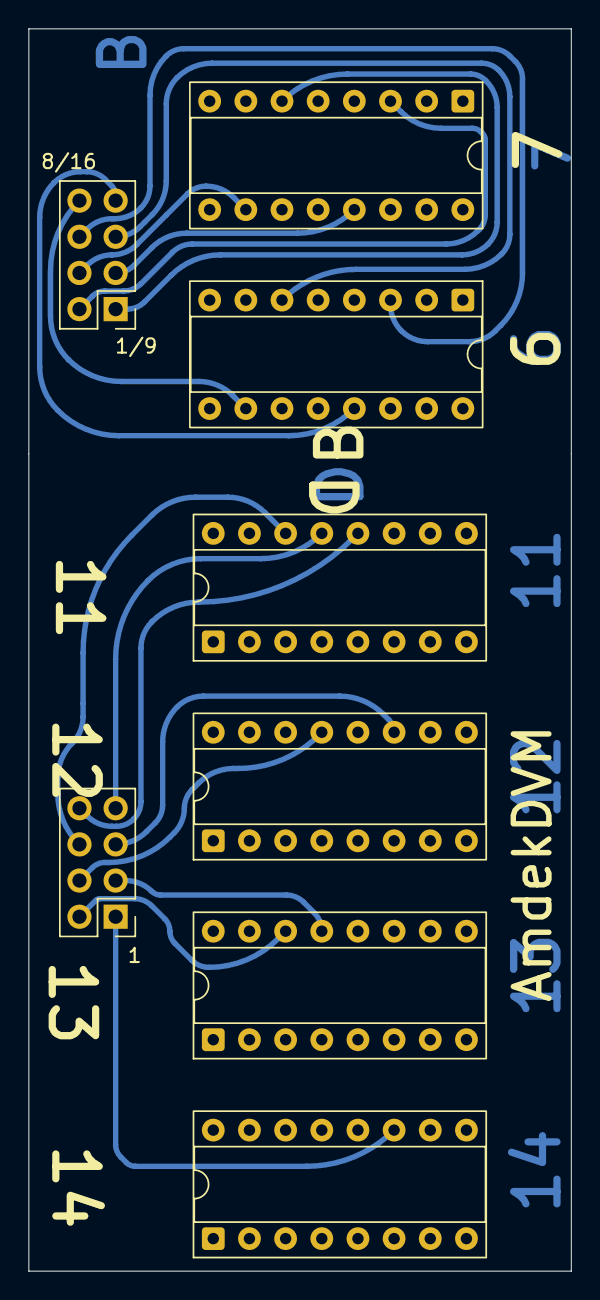
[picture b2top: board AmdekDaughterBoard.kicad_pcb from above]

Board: 2 copper layers, 38.1 x 87.2 mm, 8 parts (0 on the bottom side), 16 nets.

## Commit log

2025-04-20 Add daughterboards
2025-05-03 Add cable details, fab packages, instructions
2025-05-04 Correct video pinout

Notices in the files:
AmdekDVM.kicad_pcb:
RE © 2025 Tube Time
